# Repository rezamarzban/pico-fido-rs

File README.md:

# pico-fido-rs

A FIDO2 / U2F security key for the Raspberry Pi Pico (RP2040), written in Rust with Embassy. The CTAP
protocol itself is **Google's OpenSK library** (Apache-2.0); this repository is the RP2040 platform layer
around it (USB, flash store, button, RNG). This branch adds a PIN-wrapped master-key vault to the OpenSK-based firmware. **Experimental. Built and tested on a Raspberry Pi Pico (Linux, Windows, Android). Read `SECURITY.md` before relying on it.**

## Architecture
| Part | Where |
|------|-------|
| CTAP2 / CTAP1 (U2F), CTAPHID, ClientPIN, credential logic | OpenSK, `third_party/OpenSK/libraries/opensk` (fetched by `third_party/setup-opensk.sh`, not a git submodule; commit in `third_party/OPENSK_REV`) |
| `opensk::env::Env` for the Pico | `src/env/mod.rs` (`PicoEnv`; customization: minimum PIN length 10, batch attestation off) |
| Persistent store (credentials, metadata, PIN length) | `src/env/persist.rs` + `src/env/flash_store.rs`, on the `wasefire-store` crate (cleartext backend) |
| Hardening: master key + resident-credential encryption, PIN check (AES-256-GCM tag, no stored PIN hash), retry counter | `src/env/harden.rs` (`HardenPersist`), `src/vault.rs`, `src/store.rs`, `src/wrap.rs`; PIN hook in `third_party/opensk-harden.patch` |
| User presence = fresh BOOTSEL press | `src/env/user_presence.rs` |
| Packet bridge between USB (async) and OpenSK (blocking) | `src/env/hid.rs` (two queues) |
| Random numbers | `src/env/rng.rs` -> `src/keys.rs` (ring oscillator + SHA-256, `src/health.rs` health tests) |
| Clock | `src/env/clock.rs` |
| USB device, LED, main loop | `src/usb/`, `src/main.rs` |

OpenSK blocks (waiting for the button, computing signatures), so it runs in thread mode. USB, the LED and the
packet pump run on a **higher-priority interrupt executor** (`SWI_IRQ_1`), so USB keeps being serviced
meanwhile. OpenSK features enabled: `ctap1` (U2F), `config_command`, `software_crypto` (RustCrypto, ES256).
What the device really reports is whatever `authenticatorGetInfo` returns (`fido2-token -I`).

## OpenSK version
The commit is pinned in **`third_party/OPENSK_REV`** (`7b369f097dfa55b84ff9f37d2b176c6ec13c308d`, upstream `develop` of 2026-11-18, "Support uvCountSinceLastPinEntry in GetInfo (#842)"). Always build
the pinned commit: an unpinned OpenSK (for example a branch name) can change between builds. When you update the
pin, rebuild, retest on hardware and update the file.

## Flash layout
The **last 92 KiB** of flash are kept out of the linker's FLASH region (`build.rs`):
* the last **12 KiB** (`VAULT_BYTES`) are the vault: `[PIN retry counter][seed slot 0][seed slot 1]` (`src/vault.rs`);
* the **8 KiB** below it (`PUF_BYTES`, two 4 KiB helper slots, see "SRAM PUF") hold the SRAM-PUF helper data (`src/puf.rs`);
* the **72 KiB** below that (18 pages of 4 KiB, `STORE_PAGES`) are the OpenSK key-value store. (Older images used 19 pages and one 4 KiB PUF sector: a device flashed with them must be erased and reset, the store is re-formatted.)

With the `sram_puf` feature (default) `build.rs` also takes the first 512 bytes of RAM out of the linker's RAM: no
section, heap or stack ever touches them. The PUF samples this region at start-up and again every time the PUF secret is
reconstructed (PIN checks, set PIN, reset), so nothing may ever write to it.

`build.rs` derives everything from the single `flash_*` feature, so firmware, store and vault cannot overlap.
The store lost one page to the PUF sector, so an existing device **reformats its key-value store** on the first boot of
this version (resident credentials are lost; the seed in the vault survives and is bound to the PUF at that boot). This
layout differs from the earlier branches: **erase the whole flash before the first install** on a fresh device (a vault sector
holding old data is reported as damaged and the device refuses to work until a CTAP reset). On first boot a blank
vault gets a fresh random seed; a store area the store does not understand is erased once.

## Build
Needs the **nightly** pinned in `rust-toolchain.toml` (`nightly-2026-06-03`, the one OpenSK pins; OpenSK is
edition 2024). There is no stable firmware build. Release builds are size-optimised (`opt-level = "s"`, LTO,
stripped).

    # one-time: fetch OpenSK at the pinned commit into third_party/OpenSK and apply the hardening patch
    # (a plain clone, not a git submodule; its nested submodules are never fetched)
    sh third_party/setup-opensk.sh

    cargo build --release                       # 2 MiB board; USB serial number off (default)
    cargo build --release --no-default-features \
        --features rp2040_board,flash_4m,usb_serial   # e.g. a 4 MiB board with a USB serial number

Enable **exactly one** `flash_*` feature (`flash_2m`, `flash_4m`, `flash_8m`, `flash_16m`) and pick the size that
matches your board; do not use `--all-features`. `usb_serial` adds the flash unique ID as the USB serial number
(off by default: it lets hosts recognise the device across connections).

**Commit `Cargo.lock`.** There is none in this tree (it needs a successful build to generate); without it every build resolves
the newest crates, so the same source can produce different firmware at different times. Generate it with a successful build and
commit it; `build.sh` then builds `--locked` only.

### One-command UF2 build (`build.sh`)
`bash build.sh [-s 2|4|8|16] [-u] [-t TOOLCHAIN] [-r REPO_URL] [-b BRANCH] [-o OUT_DIR]` clones the repository,
fetches OpenSK at the pinned commit , installs the toolchain and `elf2uf2-rs`, builds with
the right `--features` (`-s` flash size in MiB, `-u` adds the USB serial number) and writes
`out/pico-fido-rs-<N>m.uf2`. Hold BOOTSEL while plugging in and copy the file to the `RPI-RP2` drive. It builds the
*committed* revision of the repository. **The default `-b` is `openSK-based-se5`** (this branch); pass `-b` to build another branch. With a committed `Cargo.lock` the script builds with `--locked` only and fails instead of resolving newer crates; without one it warns and builds unlocked. This script itself was only syntax-checked; the maintainer's Colab build
(same toolchain and features) is what was run on hardware.

## Stack protection and measurement
The firmware is linked with [`flip-link`](https://github.com/knurling-rs/flip-link) (`.cargo/config.toml`; `cargo install flip-link --locked`,
done by `build.sh` and CI). It puts the stack below the statics, so an overflow faults instead of overwriting the heap or the secret-guard
state. To measure the real headroom build a development image with `--features stack_probe`: it paints the unused stack at boot and logs
`stack: peak N of M bytes` (defmt) whenever the peak grows, so run PIN, makeCredential, getAssertion (resident and not) and large-blob
flows and read the log. Not measured yet.

## U2F attestation
U2F registration needs an attestation key and certificate, which this firmware does not contain. OpenSK provides
`tools/configure.py` (uses the `config_command` feature) to write them; that path was not tried here.
`use_batch_attestation` is off, so FIDO2 registrations use self attestation.

## PIN and key protection
At least **10 code points** (`default_min_pin_length` in `src/env/mod.rs`). Set it with any FIDO2 client
(`fido2-token -S`, `ykman fido access change-pin`, Chrome/Windows security-key settings).

With a PIN set, the 32-byte master seed is encrypted with **AES-256-GCM** (key = HMAC-SHA-256 of the PIN hash, `src/wrap.rs`; no memory-hard KDF) and no PIN hash is stored; a wrong PIN is detected by the GCM tag, so no separate PIN
verifier exists. The 128 bytes of OpenSK master keys
are derived on demand from the seed, which after a correct PIN lives in RAM only as XOR shares (see **RAM
guard** below) and is dropped on USB reset / suspend / unplug. Resident
credentials are encrypted under keys derived from the master. The PIN retry counter (8 tries) is the vault's.

## SRAM PUF
`src/puf.rs`. The power-up pattern of 496 reserved RAM bytes is turned into a device-bound key by a fuzzy extractor
(128-bit secret, 31x repetition code, helper data + 8-byte check in the PUF sector). The key is reconstructed on demand and never stored; it exists in RAM only while it is used, in `Zeroizing` buffers that are wiped when
their lifetime ends (including the temporary secret of the helper-data check). It is mixed into the key input (`HMAC(K_puf, PIN hash)`) and masks the seed of a no-PIN
record, so **a copy of the flash alone no longer allows offline PIN guessing or recovering the seed**. Records written
by an older build are bound automatically (no-PIN: at boot; PIN set: after the next correct PIN, one extra wrap). First boot enrols the PUF (needs a power-on reset, i.e. plugging the Pico in). Every boot logs the measured
bit errors (`puf: N bit errors of 3968`): read them over RTT on your chip before trusting it. If the key cannot be
recovered (power-up pattern too noisy, RAM still charged from a quick unplug), the PIN dialog fails with a hardware
error that is **not** counted as a wrong PIN: unplug for about 10 s and retry.

**Fail closed.** With `sram_puf` the key is required. A PUF failure never results in a plain or unbound seed record or
PIN record: a blank vault is only ever initialised with a PUF-bound seed (no plain seed touches flash first), an
existing unbound record is used only once it can be bound, `set_pin` refuses without the key, and a CTAP reset is
refused (nothing touched, no reset marker) unless the PUF can be (re-)enrolled on a power-on reset. A failed binding
of an existing record also locks the device (the correct PIN is accepted as such but does not unlock; the binding is
retried on the next entry). **A blank helper sector is not treated as "new device" when the vault already holds a PUF-bound
record (or is damaged / unreadable):** the firmware then does not enrol (that would create a different PUF secret and orphan the
seed), stays locked and shows the LED fault pattern until a CTAP reset on a power-on reset re-enrols. PUF-bound records carry an
HMAC tag over the masked seed, so a wrong PUF key can never yield a wrong seed silently (records from older builds without the tag
are accepted once and re-sealed at the next boot with a working key). A migration (binding an old unbound or untagged record to the PUF) counts as done only when the older record is confirmed wiped and the new
one is durable; otherwise the device locks with the LED fault pattern and the next boot retries (with the PUF required, `vault::open`
also locks while an older record cannot be wiped). Every locked state shows the fault pattern. A pending reset that fails at boot for any reason other than the missing PUF key no longer aborts the boot: the device stays locked
(LED fault pattern), the marker stays and the next boot repeats the reset. The PUF helper has two flash slots and every PUF-bound record names its slot: a re-enrolment writes the other slot, the new record is
written, and only then the old helper is erased. A power cut anywhere in a CTAP reset therefore leaves a usable (record, helper) pair, and the
next boot erases whichever helper the record does not name. While the key is unavailable no PIN attempt is counted and the retry counter is not touched. The device stays locked and the **LED shows the fault pattern: 3 short blinks, then a pause**, until a
boot with a working key. Boot does not panic on a postponed reset. The only way out without a working PUF is a build
without `sram_puf` (`build.sh -P`), which cannot read a PUF-bound record: that case is also reported by the LED. **It does not protect against anyone who can run code on the device (BOOTSEL, SWD)**: see `SECURITY.md`.

**Consequences:** after every USB reset the PIN must be entered once before *any* credential-ID operation works,
including U2F and `uv=discouraged` assertions. Without a PIN the seed is stored unwrapped in flash (masked by the SRAM PUF when that is enabled, see below). `T_COST` is untuned:
time a PIN check on hardware (the comment in `src/wrap.rs` targets roughly 0.5 to 1 s per check; that is a target,
not a measurement). See `SECURITY.md`.

## RAM guard
`src/ram_guard.rs` (pure logic) and `src/guard.rs` (firmware singleton): the master seed is held as `N` = 8 XOR
shares (`SHARES` in `guard.rs`, 4..=16, compile-time checked) in randomly chosen, non-adjacent slots of a 2 KiB
static pool whose other slots are random decoys. Shares are re-randomised by XORing fresh masks into share 0 and
share i (a refresh itself never reconstructs the secret; key use and PIN checks do, briefly, see `SECURITY.md`).
Masks come from a ChaCha20 DRBG seeded once at boot (ROSC, flash unique ID, ADC noise, timer jitter, conditioned
pool -> SHA-256) and reseeded about once a second. Temporaries are `Zeroizing`; secret types have no `Debug`.

How the refresh uses the CPU (`guard::tick_task`, on the interrupt executor, so it also runs while the main thread
signs or waits for the button):
* **Adaptive rate:** every 0.5 ms while the device is in use (a packet, a seed store or a reveal in the last 3 s),
  every 2 ms when it holds a seed but is idle, and only a 50 ms heartbeat without a seed (nothing to protect).
* **Short critical sections:** a refresh is 7 independent pair steps, each in its own critical section (about one
  ChaCha20 block and two 32-byte XORs). USB and the other interrupts are served between the steps, and the secret is
  valid after every step. `guard_log` / the display show the longest section actually measured.
* **Just in time:** the seed is revealed only inside `reveal_seed_into` / `with_seed` into a caller `Zeroizing`
  buffer (refreshed right before and after); the derived 128-byte master is written into the caller's buffer
  (`master_into`), not returned by value.
* **Scrubbing:** after every command, on a cancel, and (32 KiB) at boot, `src/scrub.rs` overwrites the dead stack
  frames below the caller with volatile stores, to remove copies left by moves and by the hash/HMAC code. Registers
  are not touched.
* **Idle:** the main thread sleeps in `wfi` between polls (`idle::poll_wait`) instead of spinning; the guard task's
  timer and the USB interrupts wake it. Time asleep is the idle share of the CPU load on the display.

More frequent refreshing does not by itself make the secret safer; see `SECURITY.md` for what the guard does and
does not buy, and the stress-test procedure below.

### Stress test (hardware)
Build with `--features guard_log,stack_probe` (defmt over RTT/probe) and run, each for several minutes:
1. a loop of `fido2-token`/browser registrations and assertions (with and without PIN) while a CPU-heavy host
   process runs: check that the logged `longest critical section` stays small and `latest tick ... late` stays
   below the USB frame time, and that no operation fails or times out;
2. USB reset / suspend / replug cycles during traffic (see "USB cancellation");
3. a long idle period with the seed held (the period must settle at 2000 us, the CPU load near 0 %);
4. current draw of the board idle (guard at 2 ms, `wfi` sleep) and under load, compared with the old build.
Record the numbers in `REVIEW.md`; none of this has been measured yet.

## Status display (SSD1306 OLED)
Feature `oled` (on by default): a 128x64 SSD1306 on **I2C0, SDA = GP16, SCL = GP17, address 0x3C** (same wiring as
the MicroPython `ssd1306.py` example), 3.3 V and GND. Without a display nothing happens (the write is not
acknowledged; it is probed again every 5 s). The status is drawn from the main thread while it waits for packets
or the button, one 128-byte page per step (about 12 ms at 100 kHz), so it never blocks USB:

```
FIDO OPEN USB OK           FIDO: LOCK / OPEN / BUSY / FAULT      USB: -- / OK / SLP
PIN SET PUF OK S1          PIN set or not; SRAM PUF OFF / BLANK / BAD / NOISY / OK and helper slot
CPU 12% UP 1:23:45         CPU load estimate (1 - time asleep, minus the guard refresh), uptime
RAM 153K/264K HP 12K       RAM in use (statics incl. the 128 KiB heap + stack + PUF bytes), heap in use
STK 1.2K PK 5.0K           stack now, peak (peak needs --features stack_probe)
GRD 1990/S P500US          RAM-guard full refreshes per second, current period
CS61US LT480US P1234       longest refresh critical section, latest tick lateness, packets handled
FW214K ST12/70K W3%        firmware size, key-value store use, erase budget used
```
The display never shows secrets. It needs `GP16`/`GP17` free (the default board uses GP25 for the LED); build
with `build.sh -O`, or `--no-default-features --features rp2040_board,flash_2m,sram_puf`, to leave it out.

**Blank screen? Check in this order.**
1. **The firmware has the feature.** `cargo build` enables `oled` by default, but `build.sh` (and any build with
   `--no-default-features`) only has what it lists: since this fix `build.sh` adds `oled` unless you pass `-O`; the
   build log prints `Cargo features: ...,oled`. Rebuild and reflash an older UF2. The RTT log then shows
   `oled: display found at 0x3C` or `oled: no display answered ...`; no `oled:` line at all means it is not compiled in.
2. **Pull-ups.** MicroPython's `machine.I2C` enables the RP2040's internal pull-ups, which is why the stock example works with
   bare modules; embassy-rp does not. `oled::init` now switches them on for GP16/GP17 and runs the bus at 100 kHz
   (`I2C_HZ`; use 400_000 only with external 4.7 kOhm pull-ups). Modules with their own pull-ups are unaffected.
3. **Wiring.** SDA = GP16 (pin 21), SCL = GP17 (pin 22), 3V3 (pin 36), GND (pin 38). Swapped SDA/SCL gives the same
   "no display answered" line. A module at address `0x3D` (some have a solder jumper) needs `ADDR` in `src/oled.rs`.
4. **Start-up timing.** The module may not answer in the first milliseconds: the firmware waits 100 ms, probes once and
   retries after 0.5 s, then every 5 s, so a late display appears by itself within a few seconds.
5. **Controller.** A 1.3" module is often an SH1106 (132 columns), not an SSD1306: the picture is then shifted by 2
   columns or garbled, but not blank. The status text appears about 0.5 s after the start.
Not tested on hardware by the author of this fix: confirm with the RTT log if it is still blank.

## USB cancellation
USB reset, suspend, disable and deconfigure call `env::hid::cancel_all()`: it bumps an epoch, forgets the seed
(with a PIN set) and flushes both queues. The user-presence wait, packet waits and `send` check the epoch, so a
pending button wait ends within 5 ms with `Canceled`, a late button press or a packet of the new session cannot
complete the old operation (a packet that was dequeued just before the reset is discarded, and every operation is stamped with the epoch under
which its packet arrived, not with the epoch at the time it starts), and the cancelled operation's responses are dropped. The main loop then calls
`Ctap::cancel_in_flight()` (patch below). A signature already being computed cannot be interrupted; its result is
discarded.

## OpenSK patch
`third_party/opensk-harden.patch` (applied by `build.sh`, or manually with `patch -p1 -d third_party/OpenSK <
third_party/opensk-harden.patch`) adds `Persist::unlock_with_pin` (default: legacy behaviour), calls it first in the default
`KeyStore::verify_pin_hash` (`api/key_store.rs`; since OpenSK #836/#838 every PIN check goes through the key store), and adds `Ctap::cancel_in_flight()` (drops the pending U2F touch, PIN tokens, HID state and
stateful commands, but keeps the power-up Reset window). `build.sh` replaces an older version of the patch.
Re-check it whenever `OPENSK_REV` changes.

## Tests
    sh host-test/run.sh     # OpenSK's own library unit tests (the protocol logic), run on the host
                            # + host-test/guard: ram_guard, vault (store.rs) and wrap (PIN wrap with AES-GCM, tamper checks, PUF-masked record) unit tests

The earlier host tests (custom CBOR, CTAPHID, PIN, key store, python-fido2 end-to-end) tested code that no longer
exists and were removed. **Nothing in this repository tests `src/env/*`, the USB bridge or the executor split**:
they are checked on hardware only.

## Verification status (be honest about it)
Reported by the maintainer (not independently verified): this branch was built and flashed to a Raspberry Pi Pico and tested on hardware, and
the OpenSK-based firmware family (this branch included) **works on Linux, Windows and Android**. The base firmware was built with the Colab script
(`nightly-2026-06-03`, `flash_2m`, no `usb_serial`, size-optimised release profile), flashed to a Pico, and
**working on Linux, Windows and Android with all tried browsers**. This is the behaviour the earlier custom
firmware did not have on Windows and Android. The maintainer did not record the details of the hardening tests (see the list below).

Checked while preparing this tree:
* The firmware patch that created `src/env/*` and the OpenSK wiring applies cleanly, and `src/`, `build.rs` and
  `rust-toolchain.toml` here are identical to it.
* The OpenSK library alone, at the pinned commit, with `ctap1,software_crypto`, type-checks for
  `thumbv6m-none-eabi` (check only).

**Hardening status:** `HardenPersist`, the vault and the patch were first written without compiling (the first build found three errors, since fixed). The branch has since been built and run on a Pico by the maintainer. **No detailed test record exists** for: Argon2 timing and heap/RAM headroom, PIN set/change/verify, resident credentials after reboot, power loss during setPIN/reset, lock on USB reset, the RAM guard, USB cancellation and vault-update checks, and the SRAM PUF (measured bit errors per boot: see `REVIEW.md`). Treat these as working in the maintainer's use but not systematically verified.

**Not done / unknown:**
* `cargo clippy -- --deny=warnings`, `cargo fmt --check` and the CI workflow were never run on this tree.
* No documented test matrix: which sites, PIN dialogs, U2F-only sites, resident keys, reset, power loss during a
  flash write, P-256 signing time, RAM headroom (128 KiB heap), and RNG health tests on a real ring oscillator.
* `build.sh` end to end, and U2F attestation provisioning.
* USB VID/PID (`0xc0de:0xcafe`) and strings are prototype placeholders (`src/usb/mod.rs`).

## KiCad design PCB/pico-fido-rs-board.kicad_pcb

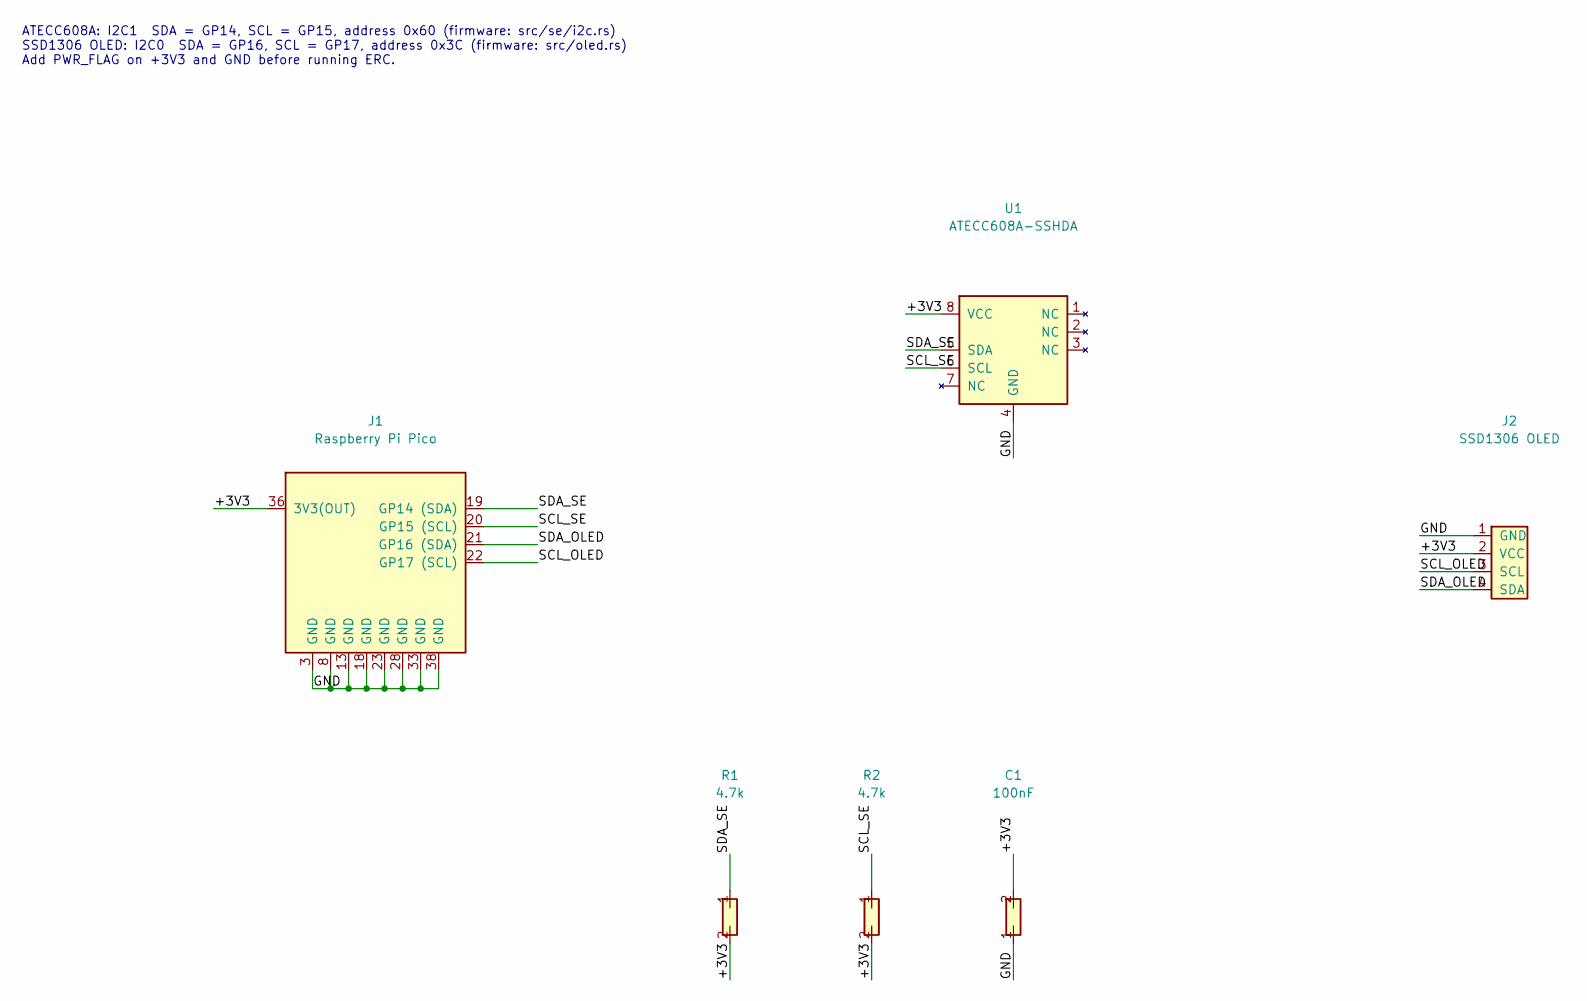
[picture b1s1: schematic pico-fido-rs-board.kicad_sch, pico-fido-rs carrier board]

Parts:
C1: 100nF; C_0805_2012Metric
J1: Raspberry Pi Pico; Pico_THT_2x20_P2.54mm
J2: SSD1306 OLED; PinHeader_1x04_P2.54mm_Vertical
R1, R2: 4.7k; R_0805_2012Metric
U1: ATECC608A-SSHDA; SOIC-8_3.9x4.9mm_P1.27mm

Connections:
+3V3: C1.2, J1.36 (3V3(OUT)), J2.2 (VCC), R1.2, R2.2, U1.8 (VCC)
GND: C1.1, J1.3 (GND), J1.8 (GND), J1.13 (GND), J1.18 (GND), J1.23 (GND), J1.28 (GND), J1.33 (GND), J1.38 (GND), J2.1 (GND), U1.4 (GND)
SCL_OLED: J1.22 (GP17 (SCL)), J2.3 (SCL)
SCL_SE: J1.20 (GP15 (SCL)), R2.1, U1.6 (SCL)
SDA_OLED: J1.21 (GP16 (SDA)), J2.4 (SDA)
SDA_SE: J1.19 (GP14 (SDA)), R1.1, U1.5 (SDA)

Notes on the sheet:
ATECC608A: I2C1 SDA = GP14, SCL = GP15, address 0x60 (firmware: src/se/i2c.rs) SSD1306 OLED: I2C0 SDA = GP16, SCL = GP17, address 0x3C (firmware: src/oled.rs) Add PWR_FLAG on +3V3 and GND before running ERC.

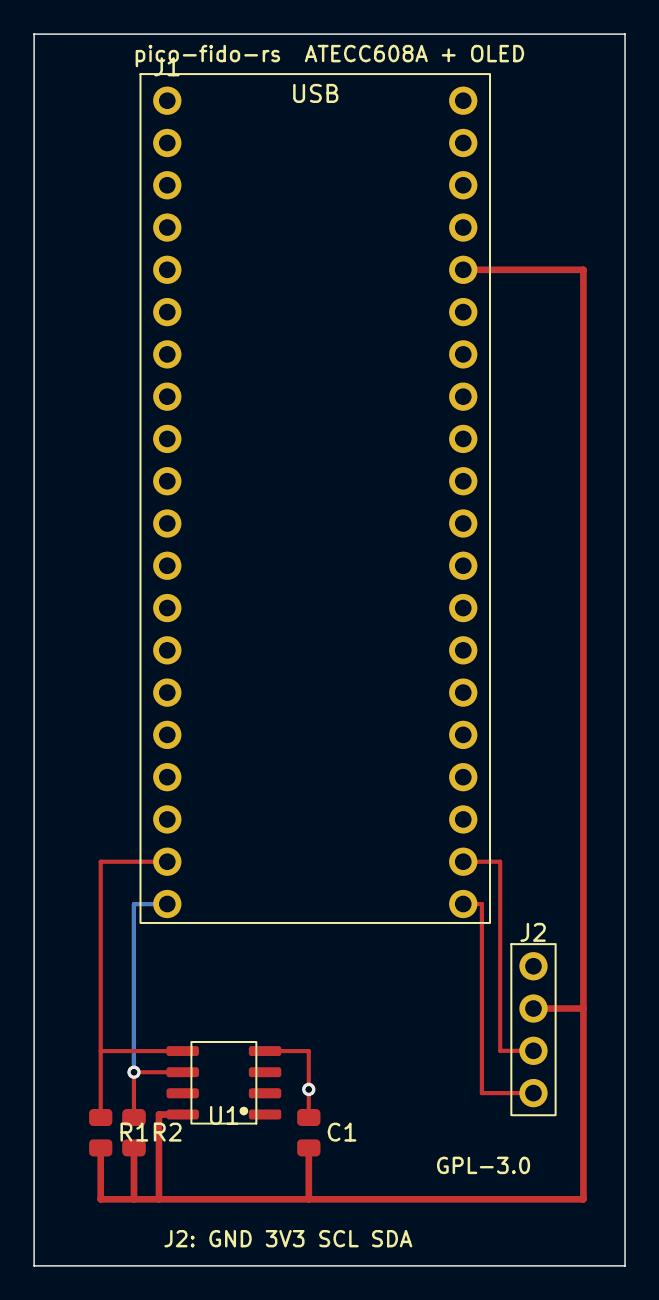
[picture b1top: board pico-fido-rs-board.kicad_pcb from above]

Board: 2 copper layers, 35.5 x 74.0 mm, 6 parts (0 on the bottom side), 6 nets.

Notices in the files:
PCB/pico-fido-rs-board.kicad_pcb:
GPL-3.0
